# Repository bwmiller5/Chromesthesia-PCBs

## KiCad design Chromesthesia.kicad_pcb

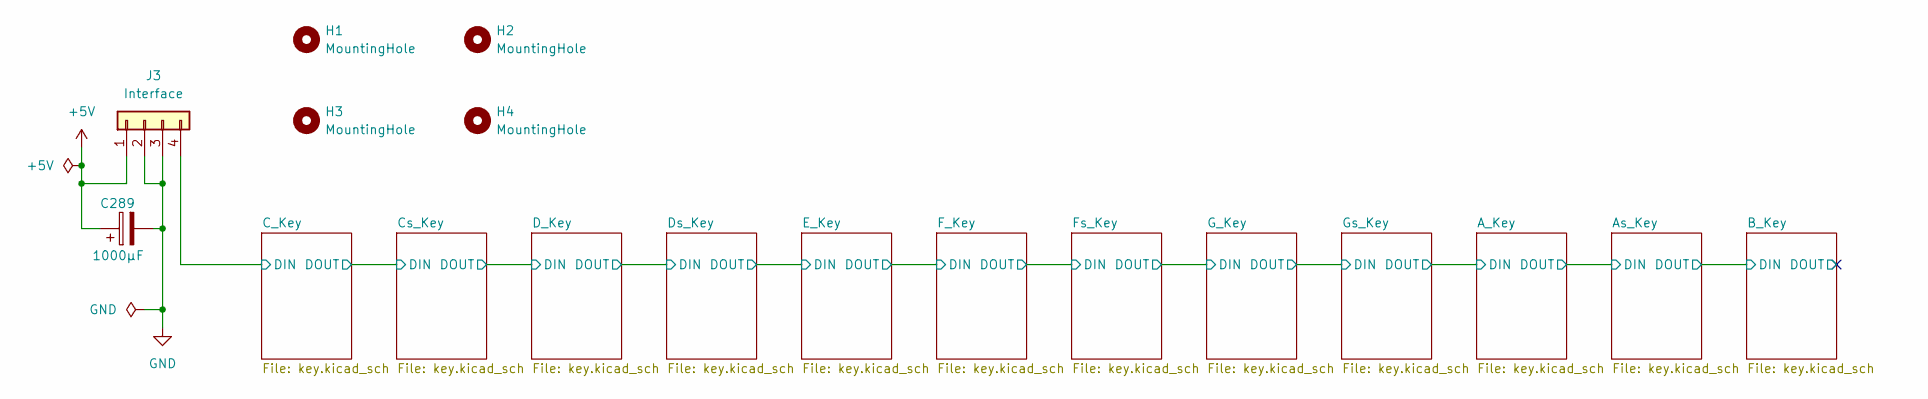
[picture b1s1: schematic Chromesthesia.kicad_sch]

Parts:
C289: 1000µF; CP_Radial_D10.0mm_P5.00mm
H1, H2, H3, H4: MountingHole; MountingHole_2.2mm_M2
J3: Interface; JST_VH_B4P-VH-FB-B_1x04_P3.96mm_Vertical

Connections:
+5V: C289.1, J3.1; also elsewhere on the board
/C_Key/DIN: J3.4; also elsewhere on the board
GND: C289.2, J3.2, J3.3; also elsewhere on the board

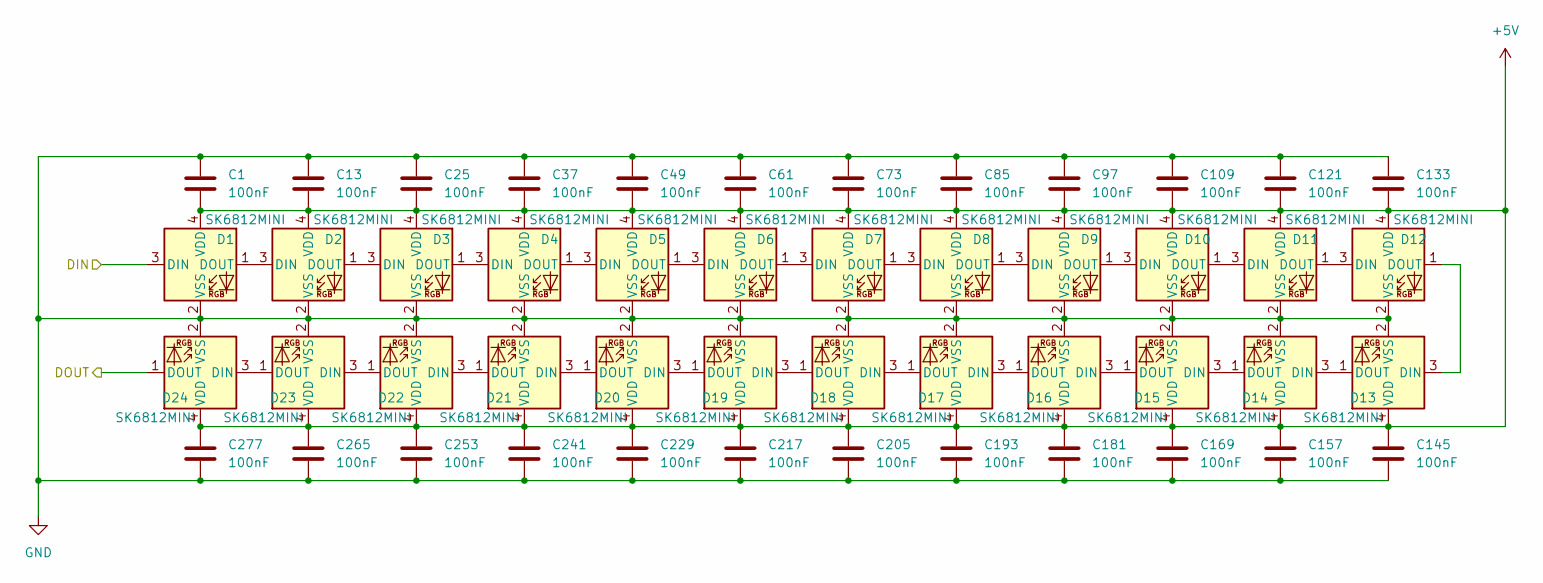
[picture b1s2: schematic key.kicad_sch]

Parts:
C1, C13, C25, C37, C49, C61, C73, C85, C97, C109, C121, C133, C145, C157, C169, C181, C193, C205, C217, C229, C241, C253, C265, C277: 100nF; C_0603_1608Metric
D1, D2, D3, D4, D5, D6, D7, D8, D9, D10, D11, D12, D13, D14, D15, D16, D17, D18, D19, D20, D21, D22, D23, D24: SK6812MINI; LED_SK6812MINI_PLCC4_3.5x3.5mm_P1.75mm

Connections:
+5V: C1.2, C13.2, C25.2, C37.2, C49.2, C61.2, C73.2, C85.2, C97.2, C109.2, C121.2, C133.2, C145.1, C157.1, C169.1, C181.1, C193.1, C205.1, C217.1, C229.1, C241.1, C253.1, C265.1, C277.1, D1.4 (VDD), D2.4 (VDD), D3.4 (VDD), D4.4 (VDD), D5.4 (VDD), D6.4 (VDD), D7.4 (VDD), D8.4 (VDD), D9.4 (VDD), D10.4 (VDD), D11.4 (VDD), D12.4 (VDD), D13.4 (VDD), D14.4 (VDD), D15.4 (VDD), D16.4 (VDD), D17.4 (VDD), D18.4 (VDD), D19.4 (VDD), D20.4 (VDD), D21.4 (VDD), D22.4 (VDD), D23.4 (VDD), D24.4 (VDD); also elsewhere on the board
/C_Key/DIN: D1.3 (DIN); also elsewhere on the board
/C_Key/DOUT: D24.1 (DOUT); also elsewhere on the board
GND: C1.1, C13.1, C25.1, C37.1, C49.1, C61.1, C73.1, C85.1, C97.1, C109.1, C121.1, C133.1, C145.2, C157.2, C169.2, C181.2, C193.2, C205.2, C217.2, C229.2, C241.2, C253.2, C265.2, C277.2, D1.2 (VSS), D2.2 (VSS), D3.2 (VSS), D4.2 (VSS), D5.2 (VSS), D6.2 (VSS), D7.2 (VSS), D8.2 (VSS), D9.2 (VSS), D10.2 (VSS), D11.2 (VSS), D12.2 (VSS), D13.2 (VSS), D14.2 (VSS), D15.2 (VSS), D16.2 (VSS), D17.2 (VSS), D18.2 (VSS), D19.2 (VSS), D20.2 (VSS), D21.2 (VSS), D22.2 (VSS), D23.2 (VSS), D24.2 (VSS); also elsewhere on the board
unnamed: D1.1 (DOUT), D2.3 (DIN)
unnamed: D2.1 (DOUT), D3.3 (DIN)
unnamed: D3.1 (DOUT), D4.3 (DIN)
unnamed: D4.1 (DOUT), D5.3 (DIN)
unnamed: D5.1 (DOUT), D6.3 (DIN)
unnamed: D6.1 (DOUT), D7.3 (DIN)
unnamed: D7.1 (DOUT), D8.3 (DIN)
unnamed: D8.1 (DOUT), D9.3 (DIN)
unnamed: D9.1 (DOUT), D10.3 (DIN)
unnamed: D10.1 (DOUT), D11.3 (DIN)
unnamed: D11.1 (DOUT), D12.3 (DIN)
unnamed: D12.1 (DOUT), D13.3 (DIN)
unnamed: D13.1 (DOUT), D14.3 (DIN)
unnamed: D14.1 (DOUT), D15.3 (DIN)
unnamed: D15.1 (DOUT), D16.3 (DIN)
unnamed: D16.1 (DOUT), D17.3 (DIN)
unnamed: D17.1 (DOUT), D18.3 (DIN)
unnamed: D18.1 (DOUT), D19.3 (DIN)
unnamed: D19.1 (DOUT), D20.3 (DIN)
unnamed: D20.1 (DOUT), D21.3 (DIN)
unnamed: D21.1 (DOUT), D22.3 (DIN)
unnamed: D22.1 (DOUT), D23.3 (DIN)
unnamed: D23.1 (DOUT), D24.3 (DIN)

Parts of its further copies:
C2, C3, C4, C5, C6, C7, C8, C9, C10, C11, C12, C14, C15, C16, C17, C18, C19, C20, C21, C22, C23, C24, C26, C27, C28, C29, C30, C31, C32, C33, C34, C35, C36, C38, C39, C40, C41, C42, C43, C44, C45, C46, C47, C48, C50, C51, C52, C53, C54, C55, C56, C57, C58, C59, C60, C62, C63, C64, C65, C66, C67, C68, C69, C70, C71, C72, C74, C75, C76, C77, C78, C79, C80, C81, C82, C83, C84, C86, C87, C88, C89, C90, C91, C92, C93, C94, C95, C96, C98, C99, C100, C101, C102, C103, C104, C105, C106, C107, C108, C110, C111, C112, C113, C114, C115, C116, C117, C118, C119, C120, C122, C123, C124, C125, C126, C127, C128, C129, C130, C131, C132, C134, C135, C136, C137, C138, C139, C140, C141, C142, C143, C144, C146, C147, C148, C149, C150, C151, C152, C153, C154, C155, C156, C158, C159, C160, C161, C162, C163, C164, C165, C166, C167, C168, C170, C171, C172, C173, C174, C175, C176, C177, C178, C179, C180, C182, C183, C184, C185, C186, C187, C188, C189, C190, C191, C192, C194, C195, C196, C197, C198, C199, C200, C201, C202, C203, C204, C206, C207, C208, C209, C210, C211, C212, C213, C214, C215, C216, C218, C219, C220, C221, C222, C223, C224, C225, C226, C227, C228, C230, C231, C232, C233, C234, C235, C236, C237, C238, C239, C240, C242, C243, C244, C245, C246, C247, C248, C249, C250, C251, C252, C254, C255, C256, C257, C258, C259, C260, C261, C262, C263, C264, C266, C267, C268, C269, C270, C271, C272, C273, C274, C275, C276, C278, C279, C280, C281, C282, C283, C284, C285, C286, C287, C288: 100nF; C_0603_1608Metric
D25, D26, D27, D28, D29, D30, D31, D32, D33, D34, D35, D36, D37, D38, D39, D40, D41, D42, D43, D44, D45, D46, D47, D48, D49, D50, D51, D52, D53, D54, D55, D56, D57, D58, D59, D60, D61, D62, D63, D64, D65, D66, D67, D68, D69, D70, D71, D72, D73, D74, D75, D76, D77, D78, D79, D80, D81, D82, D83, D84, D85, D86, D87, D88, D89, D90, D91, D92, D93, D94, D95, D96, D97, D98, D99, D100, D101, D102, D103, D104, D105, D106, D107, D108, D109, D110, D111, D112, D113, D114, D115, D116, D117, D118, D119, D120, D121, D122, D123, D124, D125, D126, D127, D128, D129, D130, D131, D132, D133, D134, D135, D136, D137, D138, D139, D140, D141, D142, D143, D144, D145, D146, D147, D148, D149, D150, D151, D152, D153, D154, D155, D156, D157, D158, D159, D160, D161, D162, D163, D164, D165, D166, D167, D168, D169, D170, D171, D172, D173, D174, D175, D176, D177, D178, D179, D180, D181, D182, D183, D184, D185, D186, D187, D188, D189, D190, D191, D192, D193, D194, D195, D196, D197, D198, D199, D200, D201, D202, D203, D204, D205, D206, D207, D208, D209, D210, D211, D212, D213, D214, D215, D216, D217, D218, D219, D220, D221, D222, D223, D224, D225, D226, D227, D228, D229, D230, D231, D232, D233, D234, D235, D236, D237, D238, D239, D240, D241, D242, D243, D244, D245, D246, D247, D248, D249, D250, D251, D252, D253, D254, D255, D256, D257, D258, D259, D260, D261, D262, D263, D264, D265, D266, D267, D268, D269, D270, D271, D272, D273, D274, D275, D276, D277, D278, D279, D280, D281, D282, D283, D284, D285, D286, D287, D288: SK6812MINI; LED_SK6812MINI_PLCC4_3.5x3.5mm_P1.75mm

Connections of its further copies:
+5V: C2.2, C3.2, C4.2, C5.2, C6.2, C7.2, C8.2, C9.2, C10.2, C11.2, C12.2, C14.2, C15.2, C16.2, C17.2, C18.2, C19.2, C20.2, C21.2, C22.2, C23.2, C24.2, C26.2, C27.2, C28.2, C29.2, C30.2, C31.2, C32.2, C33.2, C34.2, C35.2, C36.2, C38.2, C39.2, C40.2, C41.2, C42.2, C43.2, C44.2, C45.2, C46.2, C47.2, C48.2, C50.2, C51.2, C52.2, C53.2, C54.2, C55.2, C56.2, C57.2, C58.2, C59.2, C60.2, C62.2, C63.2, C64.2, C65.2, C66.2, C67.2, C68.2, C69.2, C70.2, C71.2, C72.2, C74.2, C75.2, C76.2, C77.2, C78.2, C79.2, C80.2, C81.2, C82.2, C83.2, C84.2, C86.2, C87.2, C88.2, C89.2, C90.2, C91.2, C92.2, C93.2, C94.2, C95.2, C96.2, C98.2, C99.2, C100.2, C101.2, C102.2, C103.2, C104.2, C105.2, C106.2, C107.2, C108.2, C110.2, C111.2, C112.2, C113.2, C114.2, C115.2, C116.2, C117.2, C118.2, C119.2, C120.2, C122.2, C123.2, C124.2, C125.2, C126.2, C127.2, C128.2, C129.2, C130.2, C131.2, C132.2, C134.2, C135.2, C136.2, C137.2, C138.2, C139.2, C140.2, C141.2, C142.2, C143.2, C144.2, C146.1, C147.1, C148.1, C149.1, C150.1, C151.1, C152.1, C153.1, C154.1, C155.1, C156.1, C158.1, C159.1, C160.1, C161.1, C162.1, C163.1, C164.1, C165.1, C166.1, C167.1, C168.1, C170.1, C171.1, C172.1, C173.1, C174.1, C175.1, C176.1, C177.1, C178.1, C179.1, C180.1, C182.1, C183.1, C184.1, C185.1, C186.1, C187.1, C188.1, C189.1, C190.1, C191.1, C192.1, C194.1, C195.1, C196.1, C197.1, C198.1, C199.1, C200.1, C201.1, C202.1, C203.1, C204.1, C206.1, C207.1, C208.1, C209.1, C210.1, C211.1, C212.1, C213.1, C214.1, C215.1, C216.1, C218.1, C219.1, C220.1, C221.1, C222.1, C223.1, C224.1, C225.1, C226.1, C227.1, C228.1, C230.1, C231.1, C232.1, C233.1, C234.1, C235.1, C236.1, C237.1, C238.1, C239.1, C240.1, C242.1, C243.1, C244.1, C245.1, C246.1, C247.1, C248.1, C249.1, C250.1, C251.1, C252.1, C254.1, C255.1, C256.1, C257.1, C258.1, C259.1, C260.1, C261.1, C262.1, C263.1, C264.1, C266.1, C267.1, C268.1, C269.1, C270.1, C271.1, C272.1, C273.1, C274.1, C275.1, C276.1, C278.1, C279.1, C280.1, C281.1, C282.1, C283.1, C284.1, C285.1, C286.1, C287.1, C288.1, D25.4 (VDD), D26.4 (VDD), D27.4 (VDD), D28.4 (VDD), D29.4 (VDD), D30.4 (VDD), D31.4 (VDD), D32.4 (VDD), D33.4 (VDD), D34.4 (VDD), D35.4 (VDD), D36.4 (VDD), D37.4 (VDD), D38.4 (VDD), D39.4 (VDD), D40.4 (VDD), D41.4 (VDD), D42.4 (VDD), D43.4 (VDD), D44.4 (VDD), D45.4 (VDD), D46.4 (VDD), D47.4 (VDD), D48.4 (VDD), D49.4 (VDD), D50.4 (VDD), D51.4 (VDD), D52.4 (VDD), D53.4 (VDD), D54.4 (VDD), D55.4 (VDD), D56.4 (VDD), D57.4 (VDD), D58.4 (VDD), D59.4 (VDD), D60.4 (VDD), D61.4 (VDD), D62.4 (VDD), D63.4 (VDD), D64.4 (VDD), D65.4 (VDD), D66.4 (VDD), D67.4 (VDD), D68.4 (VDD), D69.4 (VDD), D70.4 (VDD), D71.4 (VDD), D72.4 (VDD), D73.4 (VDD), D74.4 (VDD), D75.4 (VDD), D76.4 (VDD), D77.4 (VDD), D78.4 (VDD), D79.4 (VDD), D80.4 (VDD), D81.4 (VDD), D82.4 (VDD), D83.4 (VDD), D84.4 (VDD), D85.4 (VDD), D86.4 (VDD), D87.4 (VDD), D88.4 (VDD), D89.4 (VDD), D90.4 (VDD), D91.4 (VDD), D92.4 (VDD), D93.4 (VDD), D94.4 (VDD), D95.4 (VDD), D96.4 (VDD), D97.4 (VDD), D98.4 (VDD), D99.4 (VDD), D100.4 (VDD), D101.4 (VDD), D102.4 (VDD), D103.4 (VDD), D104.4 (VDD), D105.4 (VDD), D106.4 (VDD), D107.4 (VDD), D108.4 (VDD), D109.4 (VDD), D110.4 (VDD), D111.4 (VDD), D112.4 (VDD), D113.4 (VDD), D114.4 (VDD), D115.4 (VDD), D116.4 (VDD), D117.4 (VDD), D118.4 (VDD), D119.4 (VDD), D120.4 (VDD), D121.4 (VDD), D122.4 (VDD), D123.4 (VDD), D124.4 (VDD), D125.4 (VDD), D126.4 (VDD), D127.4 (VDD), D128.4 (VDD), D129.4 (VDD), D130.4 (VDD), D131.4 (VDD), D132.4 (VDD), D133.4 (VDD), D134.4 (VDD), D135.4 (VDD), D136.4 (VDD), D137.4 (VDD), D138.4 (VDD), D139.4 (VDD), D140.4 (VDD), D141.4 (VDD), D142.4 (VDD), D143.4 (VDD), D144.4 (VDD), D145.4 (VDD), D146.4 (VDD), D147.4 (VDD), D148.4 (VDD), D149.4 (VDD), D150.4 (VDD), D151.4 (VDD), D152.4 (VDD), D153.4 (VDD), D154.4 (VDD), D155.4 (VDD), D156.4 (VDD), D157.4 (VDD), D158.4 (VDD), D159.4 (VDD), D160.4 (VDD), D161.4 (VDD), D162.4 (VDD), D163.4 (VDD), D164.4 (VDD), D165.4 (VDD), D166.4 (VDD), D167.4 (VDD), D168.4 (VDD), D169.4 (VDD), D170.4 (VDD), D171.4 (VDD), D172.4 (VDD), D173.4 (VDD), D174.4 (VDD), D175.4 (VDD), D176.4 (VDD), D177.4 (VDD), D178.4 (VDD), D179.4 (VDD), D180.4 (VDD), D181.4 (VDD), D182.4 (VDD), D183.4 (VDD), D184.4 (VDD), D185.4 (VDD), D186.4 (VDD), D187.4 (VDD), D188.4 (VDD), D189.4 (VDD), D190.4 (VDD), D191.4 (VDD), D192.4 (VDD), D193.4 (VDD), D194.4 (VDD), D195.4 (VDD), D196.4 (VDD), D197.4 (VDD), D198.4 (VDD), D199.4 (VDD), D200.4 (VDD), D201.4 (VDD), D202.4 (VDD), D203.4 (VDD), D204.4 (VDD), D205.4 (VDD), D206.4 (VDD), D207.4 (VDD), D208.4 (VDD), D209.4 (VDD), D210.4 (VDD), D211.4 (VDD), D212.4 (VDD), D213.4 (VDD), D214.4 (VDD), D215.4 (VDD), D216.4 (VDD), D217.4 (VDD), D218.4 (VDD), D219.4 (VDD), D220.4 (VDD), D221.4 (VDD), D222.4 (VDD), D223.4 (VDD), D224.4 (VDD), D225.4 (VDD), D226.4 (VDD), D227.4 (VDD), D228.4 (VDD), D229.4 (VDD), D230.4 (VDD), D231.4 (VDD), D232.4 (VDD), D233.4 (VDD), D234.4 (VDD), D235.4 (VDD), D236.4 (VDD), D237.4 (VDD), D238.4 (VDD), D239.4 (VDD), D240.4 (VDD), D241.4 (VDD), D242.4 (VDD), D243.4 (VDD), D244.4 (VDD), D245.4 (VDD), D246.4 (VDD), D247.4 (VDD), D248.4 (VDD), D249.4 (VDD), D250.4 (VDD), D251.4 (VDD), D252.4 (VDD), D253.4 (VDD), D254.4 (VDD), D255.4 (VDD), D256.4 (VDD), D257.4 (VDD), D258.4 (VDD), D259.4 (VDD), D260.4 (VDD), D261.4 (VDD), D262.4 (VDD), D263.4 (VDD), D264.4 (VDD), D265.4 (VDD), D266.4 (VDD), D267.4 (VDD), D268.4 (VDD), D269.4 (VDD), D270.4 (VDD), D271.4 (VDD), D272.4 (VDD), D273.4 (VDD), D274.4 (VDD), D275.4 (VDD), D276.4 (VDD), D277.4 (VDD), D278.4 (VDD), D279.4 (VDD), D280.4 (VDD), D281.4 (VDD), D282.4 (VDD), D283.4 (VDD), D284.4 (VDD), D285.4 (VDD), D286.4 (VDD), D287.4 (VDD), D288.4 (VDD); also elsewhere on the board
/A_Key/DIN: D194.1 (DOUT), D217.3 (DIN)
/A_Key/DOUT: D218.1 (DOUT), D241.3 (DIN)
/As_Key/DOUT: D242.1 (DOUT), D265.3 (DIN)
/B_Key/DOUT: D266.1 (DOUT)
/C_Key/DOUT: D25.3 (DIN); also elsewhere on the board
/Cs_Key/DOUT: D26.1 (DOUT), D49.3 (DIN)
/D_Key/DOUT: D50.1 (DOUT), D73.3 (DIN)
/Ds_Key/DOUT: D74.1 (DOUT), D97.3 (DIN)
/E_Key/DOUT: D98.1 (DOUT), D121.3 (DIN)
/F_Key/DOUT: D122.1 (DOUT), D145.3 (DIN)
/Fs_Key/DOUT: D146.1 (DOUT), D169.3 (DIN)
/G_Key/DOUT: D170.1 (DOUT), D193.3 (DIN)
GND: C2.1, C3.1, C4.1, C5.1, C6.1, C7.1, C8.1, C9.1, C10.1, C11.1, C12.1, C14.1, C15.1, C16.1, C17.1, C18.1, C19.1, C20.1, C21.1, C22.1, C23.1, C24.1, C26.1, C27.1, C28.1, C29.1, C30.1, C31.1, C32.1, C33.1, C34.1, C35.1, C36.1, C38.1, C39.1, C40.1, C41.1, C42.1, C43.1, C44.1, C45.1, C46.1, C47.1, C48.1, C50.1, C51.1, C52.1, C53.1, C54.1, C55.1, C56.1, C57.1, C58.1, C59.1, C60.1, C62.1, C63.1, C64.1, C65.1, C66.1, C67.1, C68.1, C69.1, C70.1, C71.1, C72.1, C74.1, C75.1, C76.1, C77.1, C78.1, C79.1, C80.1, C81.1, C82.1, C83.1, C84.1, C86.1, C87.1, C88.1, C89.1, C90.1, C91.1, C92.1, C93.1, C94.1, C95.1, C96.1, C98.1, C99.1, C100.1, C101.1, C102.1, C103.1, C104.1, C105.1, C106.1, C107.1, C108.1, C110.1, C111.1, C112.1, C113.1, C114.1, C115.1, C116.1, C117.1, C118.1, C119.1, C120.1, C122.1, C123.1, C124.1, C125.1, C126.1, C127.1, C128.1, C129.1, C130.1, C131.1, C132.1, C134.1, C135.1, C136.1, C137.1, C138.1, C139.1, C140.1, C141.1, C142.1, C143.1, C144.1, C146.2, C147.2, C148.2, C149.2, C150.2, C151.2, C152.2, C153.2, C154.2, C155.2, C156.2, C158.2, C159.2, C160.2, C161.2, C162.2, C163.2, C164.2, C165.2, C166.2, C167.2, C168.2, C170.2, C171.2, C172.2, C173.2, C174.2, C175.2, C176.2, C177.2, C178.2, C179.2, C180.2, C182.2, C183.2, C184.2, C185.2, C186.2, C187.2, C188.2, C189.2, C190.2, C191.2, C192.2, C194.2, C195.2, C196.2, C197.2, C198.2, C199.2, C200.2, C201.2, C202.2, C203.2, C204.2, C206.2, C207.2, C208.2, C209.2, C210.2, C211.2, C212.2, C213.2, C214.2, C215.2, C216.2, C218.2, C219.2, C220.2, C221.2, C222.2, C223.2, C224.2, C225.2, C226.2, C227.2, C228.2, C230.2, C231.2, C232.2, C233.2, C234.2, C235.2, C236.2, C237.2, C238.2, C239.2, C240.2, C242.2, C243.2, C244.2, C245.2, C246.2, C247.2, C248.2, C249.2, C250.2, C251.2, C252.2, C254.2, C255.2, C256.2, C257.2, C258.2, C259.2, C260.2, C261.2, C262.2, C263.2, C264.2, C266.2, C267.2, C268.2, C269.2, C270.2, C271.2, C272.2, C273.2, C274.2, C275.2, C276.2, C278.2, C279.2, C280.2, C281.2, C282.2, C283.2, C284.2, C285.2, C286.2, C287.2, C288.2, D25.2 (VSS), D26.2 (VSS), D27.2 (VSS), D28.2 (VSS), D29.2 (VSS), D30.2 (VSS), D31.2 (VSS), D32.2 (VSS), D33.2 (VSS), D34.2 (VSS), D35.2 (VSS), D36.2 (VSS), D37.2 (VSS), D38.2 (VSS), D39.2 (VSS), D40.2 (VSS), D41.2 (VSS), D42.2 (VSS), D43.2 (VSS), D44.2 (VSS), D45.2 (VSS), D46.2 (VSS), D47.2 (VSS), D48.2 (VSS), D49.2 (VSS), D50.2 (VSS), D51.2 (VSS), D52.2 (VSS), D53.2 (VSS), D54.2 (VSS), D55.2 (VSS), D56.2 (VSS), D57.2 (VSS), D58.2 (VSS), D59.2 (VSS), D60.2 (VSS), D61.2 (VSS), D62.2 (VSS), D63.2 (VSS), D64.2 (VSS), D65.2 (VSS), D66.2 (VSS), D67.2 (VSS), D68.2 (VSS), D69.2 (VSS), D70.2 (VSS), D71.2 (VSS), D72.2 (VSS), D73.2 (VSS), D74.2 (VSS), D75.2 (VSS), D76.2 (VSS), D77.2 (VSS), D78.2 (VSS), D79.2 (VSS), D80.2 (VSS), D81.2 (VSS), D82.2 (VSS), D83.2 (VSS), D84.2 (VSS), D85.2 (VSS), D86.2 (VSS), D87.2 (VSS), D88.2 (VSS), D89.2 (VSS), D90.2 (VSS), D91.2 (VSS), D92.2 (VSS), D93.2 (VSS), D94.2 (VSS), D95.2 (VSS), D96.2 (VSS), D97.2 (VSS), D98.2 (VSS), D99.2 (VSS), D100.2 (VSS), D101.2 (VSS), D102.2 (VSS), D103.2 (VSS), D104.2 (VSS), D105.2 (VSS), D106.2 (VSS), D107.2 (VSS), D108.2 (VSS), D109.2 (VSS), D110.2 (VSS), D111.2 (VSS), D112.2 (VSS), D113.2 (VSS), D114.2 (VSS), D115.2 (VSS), D116.2 (VSS), D117.2 (VSS), D118.2 (VSS), D119.2 (VSS), D120.2 (VSS), D121.2 (VSS), D122.2 (VSS), D123.2 (VSS), D124.2 (VSS), D125.2 (VSS), D126.2 (VSS), D127.2 (VSS), D128.2 (VSS), D129.2 (VSS), D130.2 (VSS), D131.2 (VSS), D132.2 (VSS), D133.2 (VSS), D134.2 (VSS), D135.2 (VSS), D136.2 (VSS), D137.2 (VSS), D138.2 (VSS), D139.2 (VSS), D140.2 (VSS), D141.2 (VSS), D142.2 (VSS), D143.2 (VSS), D144.2 (VSS), D145.2 (VSS), D146.2 (VSS), D147.2 (VSS), D148.2 (VSS), D149.2 (VSS), D150.2 (VSS), D151.2 (VSS), D152.2 (VSS), D153.2 (VSS), D154.2 (VSS), D155.2 (VSS), D156.2 (VSS), D157.2 (VSS), D158.2 (VSS), D159.2 (VSS), D160.2 (VSS), D161.2 (VSS), D162.2 (VSS), D163.2 (VSS), D164.2 (VSS), D165.2 (VSS), D166.2 (VSS), D167.2 (VSS), D168.2 (VSS), D169.2 (VSS), D170.2 (VSS), D171.2 (VSS), D172.2 (VSS), D173.2 (VSS), D174.2 (VSS), D175.2 (VSS), D176.2 (VSS), D177.2 (VSS), D178.2 (VSS), D179.2 (VSS), D180.2 (VSS), D181.2 (VSS), D182.2 (VSS), D183.2 (VSS), D184.2 (VSS), D185.2 (VSS), D186.2 (VSS), D187.2 (VSS), D188.2 (VSS), D189.2 (VSS), D190.2 (VSS), D191.2 (VSS), D192.2 (VSS), D193.2 (VSS), D194.2 (VSS), D195.2 (VSS), D196.2 (VSS), D197.2 (VSS), D198.2 (VSS), D199.2 (VSS), D200.2 (VSS), D201.2 (VSS), D202.2 (VSS), D203.2 (VSS), D204.2 (VSS), D205.2 (VSS), D206.2 (VSS), D207.2 (VSS), D208.2 (VSS), D209.2 (VSS), D210.2 (VSS), D211.2 (VSS), D212.2 (VSS), D213.2 (VSS), D214.2 (VSS), D215.2 (VSS), D216.2 (VSS), D217.2 (VSS), D218.2 (VSS), D219.2 (VSS), D220.2 (VSS), D221.2 (VSS), D222.2 (VSS), D223.2 (VSS), D224.2 (VSS), D225.2 (VSS), D226.2 (VSS), D227.2 (VSS), D228.2 (VSS), D229.2 (VSS), D230.2 (VSS), D231.2 (VSS), D232.2 (VSS), D233.2 (VSS), D234.2 (VSS), D235.2 (VSS), D236.2 (VSS), D237.2 (VSS), D238.2 (VSS), D239.2 (VSS), D240.2 (VSS), D241.2 (VSS), D242.2 (VSS), D243.2 (VSS), D244.2 (VSS), D245.2 (VSS), D246.2 (VSS), D247.2 (VSS), D248.2 (VSS), D249.2 (VSS), D250.2 (VSS), D251.2 (VSS), D252.2 (VSS), D253.2 (VSS), D254.2 (VSS), D255.2 (VSS), D256.2 (VSS), D257.2 (VSS), D258.2 (VSS), D259.2 (VSS), D260.2 (VSS), D261.2 (VSS), D262.2 (VSS), D263.2 (VSS), D264.2 (VSS), D265.2 (VSS), D266.2 (VSS), D267.2 (VSS), D268.2 (VSS), D269.2 (VSS), D270.2 (VSS), D271.2 (VSS), D272.2 (VSS), D273.2 (VSS), D274.2 (VSS), D275.2 (VSS), D276.2 (VSS), D277.2 (VSS), D278.2 (VSS), D279.2 (VSS), D280.2 (VSS), D281.2 (VSS), D282.2 (VSS), D283.2 (VSS), D284.2 (VSS), D285.2 (VSS), D286.2 (VSS), D287.2 (VSS), D288.2 (VSS); also elsewhere on the board
unnamed: D25.1 (DOUT), D27.3 (DIN)
unnamed: D26.3 (DIN), D28.1 (DOUT)
unnamed: D27.1 (DOUT), D29.3 (DIN)
unnamed: D28.3 (DIN), D30.1 (DOUT)
unnamed: D29.1 (DOUT), D31.3 (DIN)
unnamed: D30.3 (DIN), D32.1 (DOUT)
unnamed: D31.1 (DOUT), D33.3 (DIN)
unnamed: D32.3 (DIN), D34.1 (DOUT)
unnamed: D33.1 (DOUT), D35.3 (DIN)
unnamed: D34.3 (DIN), D36.1 (DOUT)
unnamed: D35.1 (DOUT), D37.3 (DIN)
unnamed: D36.3 (DIN), D38.1 (DOUT)
unnamed: D37.1 (DOUT), D39.3 (DIN)
unnamed: D38.3 (DIN), D40.1 (DOUT)
unnamed: D39.1 (DOUT), D41.3 (DIN)
unnamed: D40.3 (DIN), D42.1 (DOUT)
unnamed: D41.1 (DOUT), D43.3 (DIN)
unnamed: D42.3 (DIN), D44.1 (DOUT)
unnamed: D43.1 (DOUT), D45.3 (DIN)
unnamed: D44.3 (DIN), D46.1 (DOUT)
unnamed: D45.1 (DOUT), D47.3 (DIN)
unnamed: D46.3 (DIN), D48.1 (DOUT)
unnamed: D47.1 (DOUT), D48.3 (DIN)
unnamed: D49.1 (DOUT), D51.3 (DIN)
unnamed: D50.3 (DIN), D52.1 (DOUT)
unnamed: D51.1 (DOUT), D53.3 (DIN)
unnamed: D52.3 (DIN), D54.1 (DOUT)
unnamed: D53.1 (DOUT), D55.3 (DIN)
unnamed: D54.3 (DIN), D56.1 (DOUT)
unnamed: D55.1 (DOUT), D57.3 (DIN)
unnamed: D56.3 (DIN), D58.1 (DOUT)
unnamed: D57.1 (DOUT), D59.3 (DIN)
unnamed: D58.3 (DIN), D60.1 (DOUT)
unnamed: D59.1 (DOUT), D61.3 (DIN)
unnamed: D60.3 (DIN), D62.1 (DOUT)
unnamed: D61.1 (DOUT), D63.3 (DIN)
unnamed: D62.3 (DIN), D64.1 (DOUT)
unnamed: D63.1 (DOUT), D65.3 (DIN)
unnamed: D64.3 (DIN), D66.1 (DOUT)
unnamed: D65.1 (DOUT), D67.3 (DIN)
unnamed: D66.3 (DIN), D68.1 (DOUT)
unnamed: D67.1 (DOUT), D69.3 (DIN)
unnamed: D68.3 (DIN), D70.1 (DOUT)
unnamed: D69.1 (DOUT), D71.3 (DIN)
unnamed: D70.3 (DIN), D72.1 (DOUT)
unnamed: D71.1 (DOUT), D72.3 (DIN)
unnamed: D73.1 (DOUT), D75.3 (DIN)
unnamed: D74.3 (DIN), D76.1 (DOUT)
unnamed: D75.1 (DOUT), D77.3 (DIN)
unnamed: D76.3 (DIN), D78.1 (DOUT)
unnamed: D77.1 (DOUT), D79.3 (DIN)
unnamed: D78.3 (DIN), D80.1 (DOUT)
unnamed: D79.1 (DOUT), D81.3 (DIN)
unnamed: D80.3 (DIN), D82.1 (DOUT)
unnamed: D81.1 (DOUT), D83.3 (DIN)
unnamed: D82.3 (DIN), D84.1 (DOUT)
unnamed: D83.1 (DOUT), D85.3 (DIN)
unnamed: D84.3 (DIN), D86.1 (DOUT)
unnamed: D85.1 (DOUT), D87.3 (DIN)
unnamed: D86.3 (DIN), D88.1 (DOUT)
unnamed: D87.1 (DOUT), D89.3 (DIN)
unnamed: D88.3 (DIN), D90.1 (DOUT)
unnamed: D89.1 (DOUT), D91.3 (DIN)
unnamed: D90.3 (DIN), D92.1 (DOUT)
unnamed: D91.1 (DOUT), D93.3 (DIN)
unnamed: D92.3 (DIN), D94.1 (DOUT)
unnamed: D93.1 (DOUT), D95.3 (DIN)
unnamed: D94.3 (DIN), D96.1 (DOUT)
unnamed: D95.1 (DOUT), D96.3 (DIN)
unnamed: D97.1 (DOUT), D99.3 (DIN)
unnamed: D100.3 (DIN), D102.1 (DOUT)
unnamed: D98.3 (DIN), D100.1 (DOUT)
unnamed: D99.1 (DOUT), D101.3 (DIN)
unnamed: D101.1 (DOUT), D103.3 (DIN)
unnamed: D102.3 (DIN), D104.1 (DOUT)
unnamed: D103.1 (DOUT), D105.3 (DIN)
unnamed: D104.3 (DIN), D106.1 (DOUT)
unnamed: D105.1 (DOUT), D107.3 (DIN)
unnamed: D106.3 (DIN), D108.1 (DOUT)
unnamed: D107.1 (DOUT), D109.3 (DIN)
unnamed: D108.3 (DIN), D110.1 (DOUT)
unnamed: D109.1 (DOUT), D111.3 (DIN)
unnamed: D110.3 (DIN), D112.1 (DOUT)
unnamed: D111.1 (DOUT), D113.3 (DIN)
unnamed: D112.3 (DIN), D114.1 (DOUT)
unnamed: D113.1 (DOUT), D115.3 (DIN)
unnamed: D114.3 (DIN), D116.1 (DOUT)
unnamed: D115.1 (DOUT), D117.3 (DIN)
unnamed: D116.3 (DIN), D118.1 (DOUT)
unnamed: D117.1 (DOUT), D119.3 (DIN)
unnamed: D118.3 (DIN), D120.1 (DOUT)
unnamed: D119.1 (DOUT), D120.3 (DIN)
unnamed: D121.1 (DOUT), D123.3 (DIN)
unnamed: D122.3 (DIN), D124.1 (DOUT)
unnamed: D123.1 (DOUT), D125.3 (DIN)
unnamed: D124.3 (DIN), D126.1 (DOUT)
unnamed: D125.1 (DOUT), D127.3 (DIN)
unnamed: D126.3 (DIN), D128.1 (DOUT)
unnamed: D127.1 (DOUT), D129.3 (DIN)
unnamed: D128.3 (DIN), D130.1 (DOUT)
unnamed: D129.1 (DOUT), D131.3 (DIN)
unnamed: D130.3 (DIN), D132.1 (DOUT)
unnamed: D131.1 (DOUT), D133.3 (DIN)
unnamed: D132.3 (DIN), D134.1 (DOUT)
unnamed: D133.1 (DOUT), D135.3 (DIN)
unnamed: D134.3 (DIN), D136.1 (DOUT)
unnamed: D135.1 (DOUT), D137.3 (DIN)
unnamed: D136.3 (DIN), D138.1 (DOUT)
unnamed: D137.1 (DOUT), D139.3 (DIN)
unnamed: D138.3 (DIN), D140.1 (DOUT)
unnamed: D139.1 (DOUT), D141.3 (DIN)
unnamed: D140.3 (DIN), D142.1 (DOUT)
unnamed: D141.1 (DOUT), D143.3 (DIN)
unnamed: D142.3 (DIN), D144.1 (DOUT)
unnamed: D143.1 (DOUT), D144.3 (DIN)
unnamed: D145.1 (DOUT), D147.3 (DIN)
unnamed: D146.3 (DIN), D148.1 (DOUT)
unnamed: D147.1 (DOUT), D149.3 (DIN)
unnamed: D148.3 (DIN), D150.1 (DOUT)
unnamed: D149.1 (DOUT), D151.3 (DIN)
unnamed: D150.3 (DIN), D152.1 (DOUT)
unnamed: D151.1 (DOUT), D153.3 (DIN)
unnamed: D152.3 (DIN), D154.1 (DOUT)
unnamed: D153.1 (DOUT), D155.3 (DIN)
unnamed: D154.3 (DIN), D156.1 (DOUT)
unnamed: D155.1 (DOUT), D157.3 (DIN)
unnamed: D156.3 (DIN), D158.1 (DOUT)
unnamed: D157.1 (DOUT), D159.3 (DIN)
unnamed: D158.3 (DIN), D160.1 (DOUT)
unnamed: D159.1 (DOUT), D161.3 (DIN)
unnamed: D160.3 (DIN), D162.1 (DOUT)
unnamed: D161.1 (DOUT), D163.3 (DIN)
unnamed: D162.3 (DIN), D164.1 (DOUT)
unnamed: D163.1 (DOUT), D165.3 (DIN)
unnamed: D164.3 (DIN), D166.1 (DOUT)
unnamed: D165.1 (DOUT), D167.3 (DIN)
unnamed: D166.3 (DIN), D168.1 (DOUT)
unnamed: D167.1 (DOUT), D168.3 (DIN)
unnamed: D169.1 (DOUT), D171.3 (DIN)
unnamed: D170.3 (DIN), D172.1 (DOUT)
unnamed: D171.1 (DOUT), D173.3 (DIN)
unnamed: D172.3 (DIN), D174.1 (DOUT)
unnamed: D173.1 (DOUT), D175.3 (DIN)
unnamed: D174.3 (DIN), D176.1 (DOUT)
unnamed: D175.1 (DOUT), D177.3 (DIN)
unnamed: D176.3 (DIN), D178.1 (DOUT)
unnamed: D177.1 (DOUT), D179.3 (DIN)
unnamed: D178.3 (DIN), D180.1 (DOUT)
unnamed: D179.1 (DOUT), D181.3 (DIN)
unnamed: D180.3 (DIN), D182.1 (DOUT)
unnamed: D181.1 (DOUT), D183.3 (DIN)
unnamed: D182.3 (DIN), D184.1 (DOUT)
unnamed: D183.1 (DOUT), D185.3 (DIN)
unnamed: D184.3 (DIN), D186.1 (DOUT)
unnamed: D185.1 (DOUT), D187.3 (DIN)
unnamed: D186.3 (DIN), D188.1 (DOUT)
unnamed: D187.1 (DOUT), D189.3 (DIN)
unnamed: D188.3 (DIN), D190.1 (DOUT)
unnamed: D189.1 (DOUT), D191.3 (DIN)
unnamed: D190.3 (DIN), D192.1 (DOUT)
unnamed: D191.1 (DOUT), D192.3 (DIN)
unnamed: D193.1 (DOUT), D195.3 (DIN)
unnamed: D194.3 (DIN), D196.1 (DOUT)
unnamed: D195.1 (DOUT), D197.3 (DIN)
unnamed: D196.3 (DIN), D198.1 (DOUT)
unnamed: D197.1 (DOUT), D199.3 (DIN)
unnamed: D198.3 (DIN), D200.1 (DOUT)
unnamed: D199.1 (DOUT), D201.3 (DIN)
unnamed: D200.3 (DIN), D202.1 (DOUT)
unnamed: D201.1 (DOUT), D203.3 (DIN)
unnamed: D202.3 (DIN), D204.1 (DOUT)
unnamed: D203.1 (DOUT), D205.3 (DIN)
unnamed: D204.3 (DIN), D206.1 (DOUT)
unnamed: D205.1 (DOUT), D207.3 (DIN)
unnamed: D206.3 (DIN), D208.1 (DOUT)
unnamed: D207.1 (DOUT), D209.3 (DIN)
unnamed: D208.3 (DIN), D210.1 (DOUT)
unnamed: D209.1 (DOUT), D211.3 (DIN)
unnamed: D210.3 (DIN), D212.1 (DOUT)
unnamed: D211.1 (DOUT), D213.3 (DIN)
unnamed: D212.3 (DIN), D214.1 (DOUT)
unnamed: D213.1 (DOUT), D215.3 (DIN)
unnamed: D214.3 (DIN), D216.1 (DOUT)
unnamed: D215.1 (DOUT), D216.3 (DIN)
unnamed: D217.1 (DOUT), D219.3 (DIN)
unnamed: D218.3 (DIN), D220.1 (DOUT)
unnamed: D219.1 (DOUT), D221.3 (DIN)
unnamed: D220.3 (DIN), D222.1 (DOUT)
unnamed: D221.1 (DOUT), D223.3 (DIN)
unnamed: D222.3 (DIN), D224.1 (DOUT)
unnamed: D223.1 (DOUT), D225.3 (DIN)
unnamed: D224.3 (DIN), D226.1 (DOUT)
unnamed: D225.1 (DOUT), D227.3 (DIN)
unnamed: D226.3 (DIN), D228.1 (DOUT)
unnamed: D227.1 (DOUT), D229.3 (DIN)
unnamed: D228.3 (DIN), D230.1 (DOUT)
unnamed: D229.1 (DOUT), D231.3 (DIN)
unnamed: D230.3 (DIN), D232.1 (DOUT)
unnamed: D231.1 (DOUT), D233.3 (DIN)
unnamed: D232.3 (DIN), D234.1 (DOUT)
unnamed: D233.1 (DOUT), D235.3 (DIN)
unnamed: D234.3 (DIN), D236.1 (DOUT)
unnamed: D235.1 (DOUT), D237.3 (DIN)
unnamed: D236.3 (DIN), D238.1 (DOUT)
unnamed: D237.1 (DOUT), D239.3 (DIN)
unnamed: D238.3 (DIN), D240.1 (DOUT)
unnamed: D239.1 (DOUT), D240.3 (DIN)
unnamed: D241.1 (DOUT), D243.3 (DIN)
unnamed: D242.3 (DIN), D244.1 (DOUT)
unnamed: D243.1 (DOUT), D245.3 (DIN)
unnamed: D244.3 (DIN), D246.1 (DOUT)
unnamed: D245.1 (DOUT), D247.3 (DIN)
unnamed: D246.3 (DIN), D248.1 (DOUT)
unnamed: D247.1 (DOUT), D249.3 (DIN)
unnamed: D248.3 (DIN), D250.1 (DOUT)
unnamed: D249.1 (DOUT), D251.3 (DIN)
unnamed: D250.3 (DIN), D252.1 (DOUT)
unnamed: D251.1 (DOUT), D253.3 (DIN)
unnamed: D252.3 (DIN), D254.1 (DOUT)
unnamed: D253.1 (DOUT), D255.3 (DIN)
unnamed: D254.3 (DIN), D256.1 (DOUT)
unnamed: D255.1 (DOUT), D257.3 (DIN)
unnamed: D256.3 (DIN), D258.1 (DOUT)
unnamed: D257.1 (DOUT), D259.3 (DIN)
unnamed: D258.3 (DIN), D260.1 (DOUT)
unnamed: D259.1 (DOUT), D261.3 (DIN)
unnamed: D260.3 (DIN), D262.1 (DOUT)
unnamed: D261.1 (DOUT), D263.3 (DIN)
unnamed: D262.3 (DIN), D264.1 (DOUT)
unnamed: D263.1 (DOUT), D264.3 (DIN)
unnamed: D265.1 (DOUT), D267.3 (DIN)
unnamed: D266.3 (DIN), D268.1 (DOUT)
unnamed: D267.1 (DOUT), D269.3 (DIN)
unnamed: D268.3 (DIN), D270.1 (DOUT)
unnamed: D269.1 (DOUT), D271.3 (DIN)
unnamed: D270.3 (DIN), D272.1 (DOUT)
unnamed: D271.1 (DOUT), D273.3 (DIN)
unnamed: D272.3 (DIN), D274.1 (DOUT)
unnamed: D273.1 (DOUT), D275.3 (DIN)
unnamed: D274.3 (DIN), D276.1 (DOUT)
unnamed: D275.1 (DOUT), D277.3 (DIN)
unnamed: D276.3 (DIN), D278.1 (DOUT)
unnamed: D277.1 (DOUT), D279.3 (DIN)
unnamed: D278.3 (DIN), D280.1 (DOUT)
unnamed: D279.1 (DOUT), D281.3 (DIN)
unnamed: D280.3 (DIN), D282.1 (DOUT)
unnamed: D281.1 (DOUT), D283.3 (DIN)
unnamed: D282.3 (DIN), D284.1 (DOUT)
unnamed: D283.1 (DOUT), D285.3 (DIN)
unnamed: D284.3 (DIN), D286.1 (DOUT)
unnamed: D285.1 (DOUT), D287.3 (DIN)
unnamed: D286.3 (DIN), D288.1 (DOUT)
unnamed: D287.1 (DOUT), D288.3 (DIN)

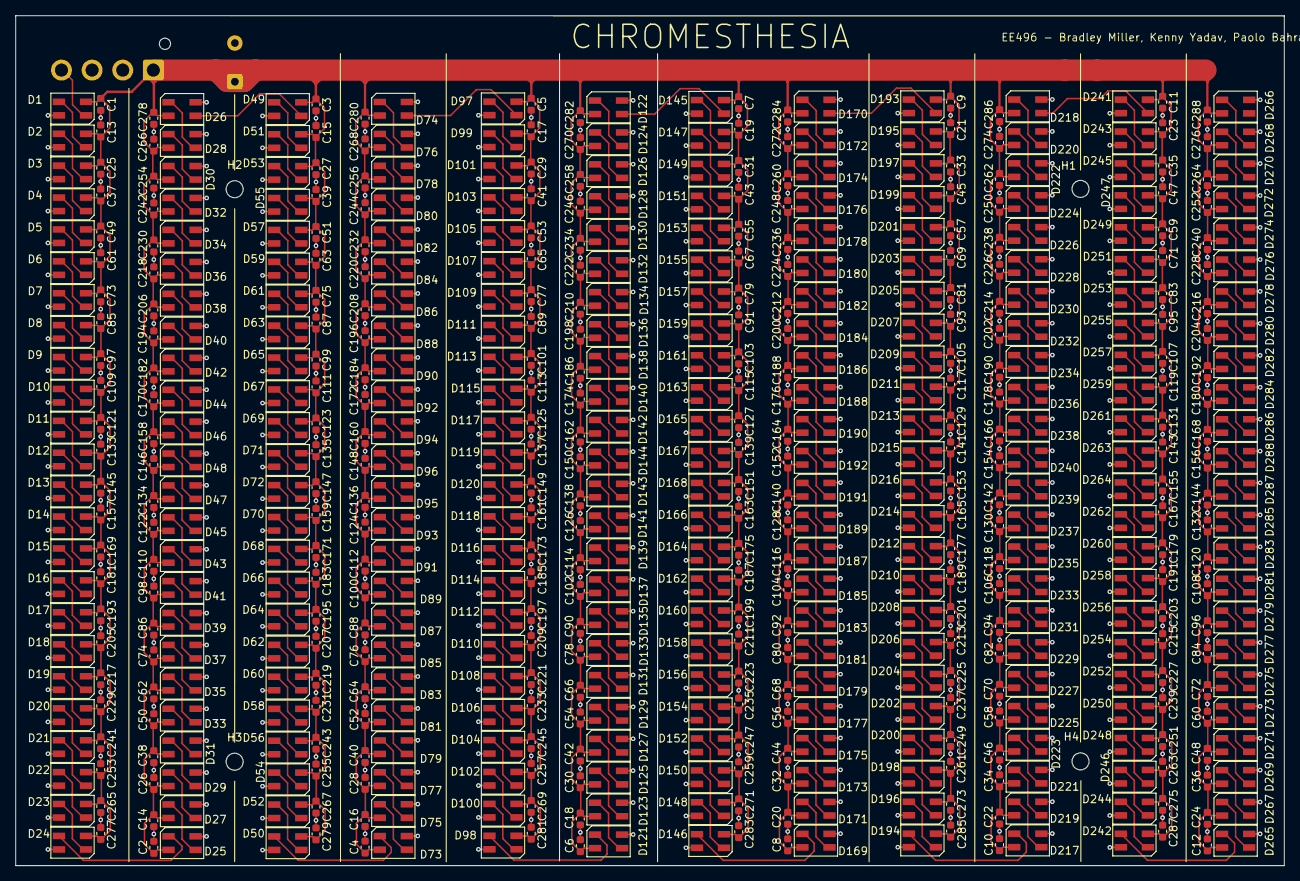
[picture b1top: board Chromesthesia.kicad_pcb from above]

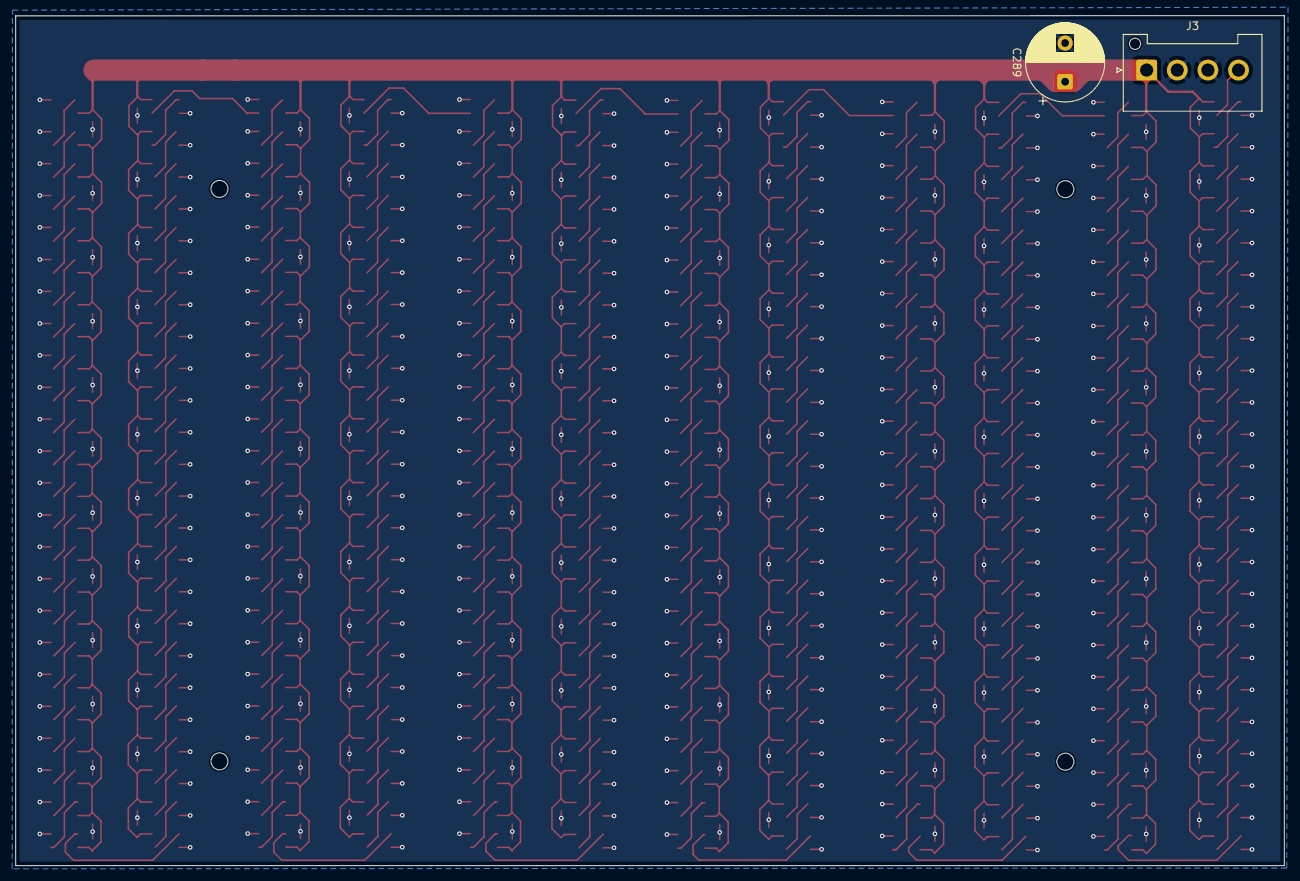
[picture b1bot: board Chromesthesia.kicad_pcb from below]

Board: 2 copper layers, 164.1 x 109.9 mm, 582 parts (2 on the bottom side), 290 nets.

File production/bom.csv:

Designator,Footprint,Quantity,Value,LCSC Part #
"C1, C10, C100, C101, C102, C103, C104, C105, C106, C107, C108, C109, C11, C110, C111, C112, C113, C114, C115, C116, C117, C118, C119, C12, C120, C121, C122, C123, C124, C125, C126, C127, C128, C129, C13, C130, C131, C132, C133, C134, C135, C136, C137, C138, C139, C14, C140, C141, C142, C143, C144, C145, C146, C147, C148, C149, C15, C150, C151, C152, C153, C154, C155, C156, C157, C158, C159, C16, C160, C161, C162, C163, C164, C165, C166, C167, C168, C169, C17, C170, C171, C172, C173, C174, C175, C176, C177, C178, C179, C18, C180, C181, C182, C183, C184, C185, C186, C187, C188, C189, C19, C190, C191, C192, C193, C194, C195, C196, C197, C198, C199, C2, C20, C200, C201, C202, C203, C204, C205, C206, C207, C208, C209, C21, C210, C211, C212, C213, C214, C215, C216, C217, C218, C219, C22, C220, C221, C222, C223, C224, C225, C226, C227, C228, C229, C23, C230, C231, C232, C233, C234, C235, C236, C237, C238, C239, C24, C240, C241, C242, C243, C244, C245, C246, C247, C248, C249, C25, C250, C251, C252, C253, C254, C255, C256, C257, C258, C259, C26, C260, C261, C262, C263, C264, C265, C266, C267, C268, C269, C27, C270, C271, C272, C273, C274, C275, C276, C277, C278, C279",0603,200,100nF,
"C28, C280, C281, C282, C283, C284, C285, C286, C287, C288, C29, C3, C30, C31, C32, C33, C34, C35, C36, C37, C38, C39, C4, C40, C41, C42, C43, C44, C45, C46, C47, C48, C49, C5, C50, C51, C52, C53, C54, C55, C56, C57, C58, C59, C6, C60, C61, C62, C63, C64, C65, C66, C67, C68, C69, C7, C70, C71, C72, C73, C74, C75, C76, C77, C78, C79, C8, C80, C81, C82, C83, C84, C85, C86, C87, C88, C89, C9, C90, C91, C92, C93, C94, C95, C96, C97, C98, C99",0603,88,100nF,
C289,CP_Radial_D10.0mm_P5.00mm,1,1000µF,
"D1, D10, D100, D101, D102, D103, D104, D105, D106, D107, D108, D109, D11, D110, D111, D112, D113, D114, D115, D116, D117, D118, D119, D12, D120, D121, D122, D123, D124, D125, D126, D127, D128, D129, D13, D130, D131, D132, D133, D134, D135, D136, D137, D138, D139, D14, D140, D141, D142, D143, D144, D145, D146, D147, D148, D149, D15, D150, D151, D152, D153, D154, D155, D156, D157, D158, D159, D16, D160, D161, D162, D163, D164, D165, D166, D167, D168, D169, D17, D170, D171, D172, D173, D174, D175, D176, D177, D178, D179, D18, D180, D181, D182, D183, D184, D185, D186, D187, D188, D189, D19, D190, D191, D192, D193, D194, D195, D196, D197, D198, D199, D2, D20, D200, D201, D202, D203, D204, D205, D206, D207, D208, D209, D21, D210, D211, D212, D213, D214, D215, D216, D217, D218, D219, D22, D220, D221, D222, D223, D224, D225, D226, D227, D228, D229, D23, D230, D231, D232, D233, D234, D235, D236, D237, D238, D239, D24, D240, D241, D242, D243, D244, D245, D246, D247, D248, D249, D25, D250, D251, D252, D253, D254, D255, D256, D257, D258, D259, D26, D260, D261, D262, D263, D264, D265, D266, D267, D268, D269, D27, D270, D271, D272, D273, D274, D275, D276, D277, D278, D279",LED_SK6812MINI_PLCC4_3.5x3.5mm_P1.75mm,200,SK6812MINI,
"D28, D280, D281, D282, D283, D284, D285, D286, D287, D288, D29, D3, D30, D31, D32, D33, D34, D35, D36, D37, D38, D39, D4, D40, D41, D42, D43, D44, D45, D46, D47, D48, D49, D5, D50, D51, D52, D53, D54, D55, D56, D57, D58, D59, D6, D60, D61, D62, D63, D64, D65, D66, D67, D68, D69, D7, D70, D71, D72, D73, D74, D75, D76, D77, D78, D79, D8, D80, D81, D82, D83, D84, D85, D86, D87, D88, D89, D9, D90, D91, D92, D93, D94, D95, D96, D97, D98, D99",LED_SK6812MINI_PLCC4_3.5x3.5mm_P1.75mm,88,SK6812MINI,
J3,JST_VH_B4P-VH-FB-B_1x04_P3.96mm_Vertical,1,Interface,

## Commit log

2026-03-31 Schematic
2026-04-02 PCB Almost Done
2026-04-03 Initial Production
2026-04-03 Warning Free Production
2026-04-03 Text Added Production
